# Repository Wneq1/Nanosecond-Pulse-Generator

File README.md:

# Nanosecond-Pulse-Generator
A nanosecond pulse generator is a device or electronic circuit designed to precisely generate pulses with extremely short durations, reaching the scale of single nanoseconds (1 ns = 10⁻⁹ seconds). Such a high time resolution is essential in many modern applications where extreme accuracy and fast operation are critical. In practice, nanosecond generators are used in measurement systems, telecommunications, and scientific research, enabling control and synchronization of very rapid processes. They allow for the generation of short electrical pulses with precisely defined pulse width and rise time, which form the foundation for high-performance digital and analog circuits.

An example waveform output from such a generator is illustrated in the graphic below. It exhibits a shape similar to a normal distribution with very steep rising and falling edges, and an amplitude close to the circuit’s supply voltage.

Although the datasheet of the LT1721 chip includes an example schematic of such a generator, it requires a triggering pulse from an external excitation generator. The author decided to design a circuit based on easily available and inexpensive components commonly found on the Polish market. Currently, the LT1721 chip is difficult to obtain in the country, which necessitates searching for alternative components.

The schematic of the generator is presented below:

The generator will consist of four basic blocks. The first block is a rectangular (square) wave signal generator. The next block is a delay line, followed by a block responsible for the exclusive alternative (exclusive OR). Finally, at the very end, there is a buffer that increases the current-driving capability of the generator’s output.

Rectangular Wave Generator Circuit:

The simplest rectangular wave generator circuit can be built using just three components: a resistor, a capacitor, and a NOT gate with a Schmitt trigger input. Circuits equipped with a Schmitt trigger input are characterized by hysteresis. Hysteresis is a phenomenon where the gate switches at different threshold voltage levels for the rising and falling edges of the signal. Therefore, for circuits with a Schmitt trigger input, threshold voltages for both edges and the hysteresis range are specified.

The simplest generator circuit is shown above. The operating principle of this circuit is very straightforward. Let’s assume that the switching thresholds of the Schmitt trigger gate are as follows: it switches from 1 to 0 when the input voltage exceeds 1.6 V, and from 0 to 1 when it drops to 0.8 V. At the very beginning, the capacitor is discharged, so the voltage at the input is 0 V, which is lower than the 0.8 V threshold required to switch from 0 to 1. Therefore, the output is at a high state. When the output is high, the capacitor starts charging through the resistor until the voltage exceeds 1.6 V, triggering a state change. This cycle repeats continuously.
The operating frequency is determined by the following formula, where C1 is the capacitance of the oscillating capacitor, and R1 is the resistance value in the feedback loop:

$f_0 = 1.2 / (R_1 * C_1)$

​Delay Line:

The primary purpose of the delay line is to deliver two signals to the exclusive OR (XOR) circuit with an appropriate time shift. In this project, the output from the generator is fed directly into the XOR gate, while the second connection is realized through two NOT gates. It should be noted that the signals at the input of the path have the same phase but are slightly delayed due to the use of the double NOT gates. The signal delay time depends solely on the propagation delays of the NOT gates used, which provide the necessary timing difference.

XOR Gate:

The XOR gate generates a short pulse (called a spike pulse) each time there is an edge on the output signal of the relaxation oscillator. Based on the XOR truth table, when its inputs are at different logic levels (one input is high while the other is delayed by the NOT inverters), the output goes high. This high state lasts until the delayed input also changes state, effectively turning off the generator. When both inputs are either high or low simultaneously, the output remains at 0, producing no pulse. These pulses appear in pairs, as each pulse corresponds to both the rising and falling edges of the oscillator’s output signal. The XOR gate is used here for precise detection of signal state changes, enabling the generation of very short output pulses.

Output Buffer:

Since the output of the generator is not intended to drive a heavy load, it was decided to increase the current-driving capability of the circuit by adding additional NOT gates at the output. The typical current capability of a standard logic gate ranges from about 5 to 10 mA, so it was necessary to increase this capacity to protect the circuit from accidental overload.
At the output of the XOR gate, there is a NOT gate that inverts the input signal. Following this, the actual buffer consists of three NOT gates connected in parallel. Resistors are placed at their outputs to provide impedance matching for the proper output, and a connector allows the addition of an external resistor if needed.

The complete generator schematic is shown below:

Selection of Integrated Circuits for the Generator:

When working with very fast logic circuits, it is crucial that their propagation delays are as short as possible. On the market, there are two main families of logic ICs widely used in digital electronics: HC (High-speed CMOS) and AC (Advanced CMOS). Both are based on CMOS technology but differ primarily in speed and power consumption, which determines their suitability for various applications. Understanding these differences helps in selecting the appropriate family of ICs for specific uses, especially in hobbyist and student projects.

The HC family, which includes ICs like the 74HC04, is characterized by low power consumption and higher speed compared to traditional CMOS devices. HC ICs are voltage-compatible with TTL logic, allowing them to be used in systems combining different logic technologies. They operate in a voltage range from 2 V to 6 V, making them versatile for low-voltage applications common in modern digital circuits. Due to their energy efficiency, HC gates are commonly used in projects requiring moderate speed with power savings.

The AC family, including ICs such as the 74AC86N, is an enhanced version of HC, offering significantly higher operating speeds. AC ICs have shorter propagation delays, making them ideal for applications requiring very fast switching. Although they consume slightly more power than HC devices, their high performance is essential in projects where response time is critical. They also operate within the same voltage range as HC (2 V to 6 V), maintaining versatility.

For the rectangular signal generator, the 74HCT14 gate was chosen because propagation delay is not a critical factor in this function, and it allows for a significant cost reduction. In contrast, the delay line and XOR modules use 74AC04N and 74AC86N gates. The use of AC gates results from more demanding tasks where delay time and XOR gate switching speed are crucial. The high-speed operation of these ICs enables precise signal control, which is especially important in this project. Additionally, the use of AC gates contributes to an energy-efficient design, with their low power consumption and simple power supply requirements (2 V to 6 V range) greatly simplifying the overall construction.

PCB Design:

The design will be carried out in the KiCad environment due to several key advantages. First and foremost, KiCad offers an intuitive and user-friendly interface that allows even beginners to start working on a project quickly. This makes the design process less time-consuming and more efficient.
Another important advantage of KiCad is the ability to visualize the project at every stage of work. This makes it easy to control the placement of components and routing of tracks, significantly minimizing the risk of errors and allowing for quick corrections. The software also provides extensive libraries of electronic components, which are regularly updated, greatly facilitating the selection and placement of the right parts. Additionally, KiCad allows easy generation of various production files such as Gerber files, drill files, and technical documentation, streamlining the process of ordering PCBs from manufacturers. It is also worth emphasizing that KiCad offers circuit simulation functionality, enabling preliminary testing of the circuit operation before creating a physical board. All these features together make using KiCad not only convenient but also economical and efficient.

The schematic is shown above, with component values indicated as well as a goldpin connector used to adjust the output resistance for proper impedance matching with the tested cable.
Below is the view of the PCB after the design phase:

Visualization of the PCB Layout:

View of the Assembled and Soldered PCB:

Demonstration of the Circuit Operation:

As shown in the image above, the generator is connected directly to the oscilloscope through a T-connector, with one output terminated using a 50-ohm resistor to ensure proper impedance matching with the tested cable. When testing a coaxial cable, the terminator is replaced with the cable under test, and the resulting waveforms are observed on the oscilloscope.

The oscilloscope waveform shown above indicates a peak amplitude of approximately 4.58 V, which is close to the supply voltage. The rise and fall times are around 1.9 ns, and the total pulse width is approximately 3.6 ns. These are satisfactory results given the components used in the circuit.

Finally, let us take a look at an example measurement that this device enables — cable length testing. In the context of such measurements, the key parameter is the propagation velocity factor, which for most cables is approximately 0.7. This value is especially important when calculating the actual length of the tested cable, as it directly affects measurement accuracy. For this test, a 1-meter coaxial cable is used.

The formula needed to calculate the cable length is:

$l = (c × v_p × t_m) / 2$

Where:
l – cable length

c – speed of light in vacuum (≈ 3×10⁸ m/s)

v_p – velocity factor (propagation speed in the medium)

t_m – time between the initial and reflected pulse

The propagation speed in coaxial cables is reduced to approximately 70% of the speed of light due to the dielectric material and the construction of the cable itself.

With all necessary data available, we can proceed with the basic calculation:

$l = (c × v_p × t_m) / 2=(3∙10^8  [m/s]∙0,7∙10,2∙10^(-9)  [s])/2=2,142 [m]/2=1,071 [m]$

Therefore, the calculated length of the cable using the time-domain reflectometry (TDR) method is 1.071 meters, which corresponds closely to the actual physical length of 1 meter, with only 0.71 centimeters of deviation — well within acceptable accuracy.

The aim of the project was to design and build a simple nanosecond pulse generator intended for studying signal propagation phenomena in long transmission lines, such as coaxial cables. The project is based on widely available and inexpensive components, making it accessible for students and hobbyists. Key parameters of the circuit, such as the pulse rise/fall time in the range of 1.7–1.9 ns and an amplitude close to the supply voltage (approx. 4.58 V), confirm its high effectiveness at a low production cost.
During the implementation, the author drew inspiration from the concept presented in the article "5ns pulse generator" from [polprog.net](https://polprog.net/blog/5nanos/5nanos.html), adapting the design to components readily available on the Polish market.
As part of the project, a custom PCB was designed, suitable logic ICs (from the HCT and AC families) were selected, necessary calculations were performed, and measurements confirmed the functionality of the circuit. In the future, the generator may be expanded with improved impedance matching, more powerful output buffers, or a microcontroller for automated cable length measurement.

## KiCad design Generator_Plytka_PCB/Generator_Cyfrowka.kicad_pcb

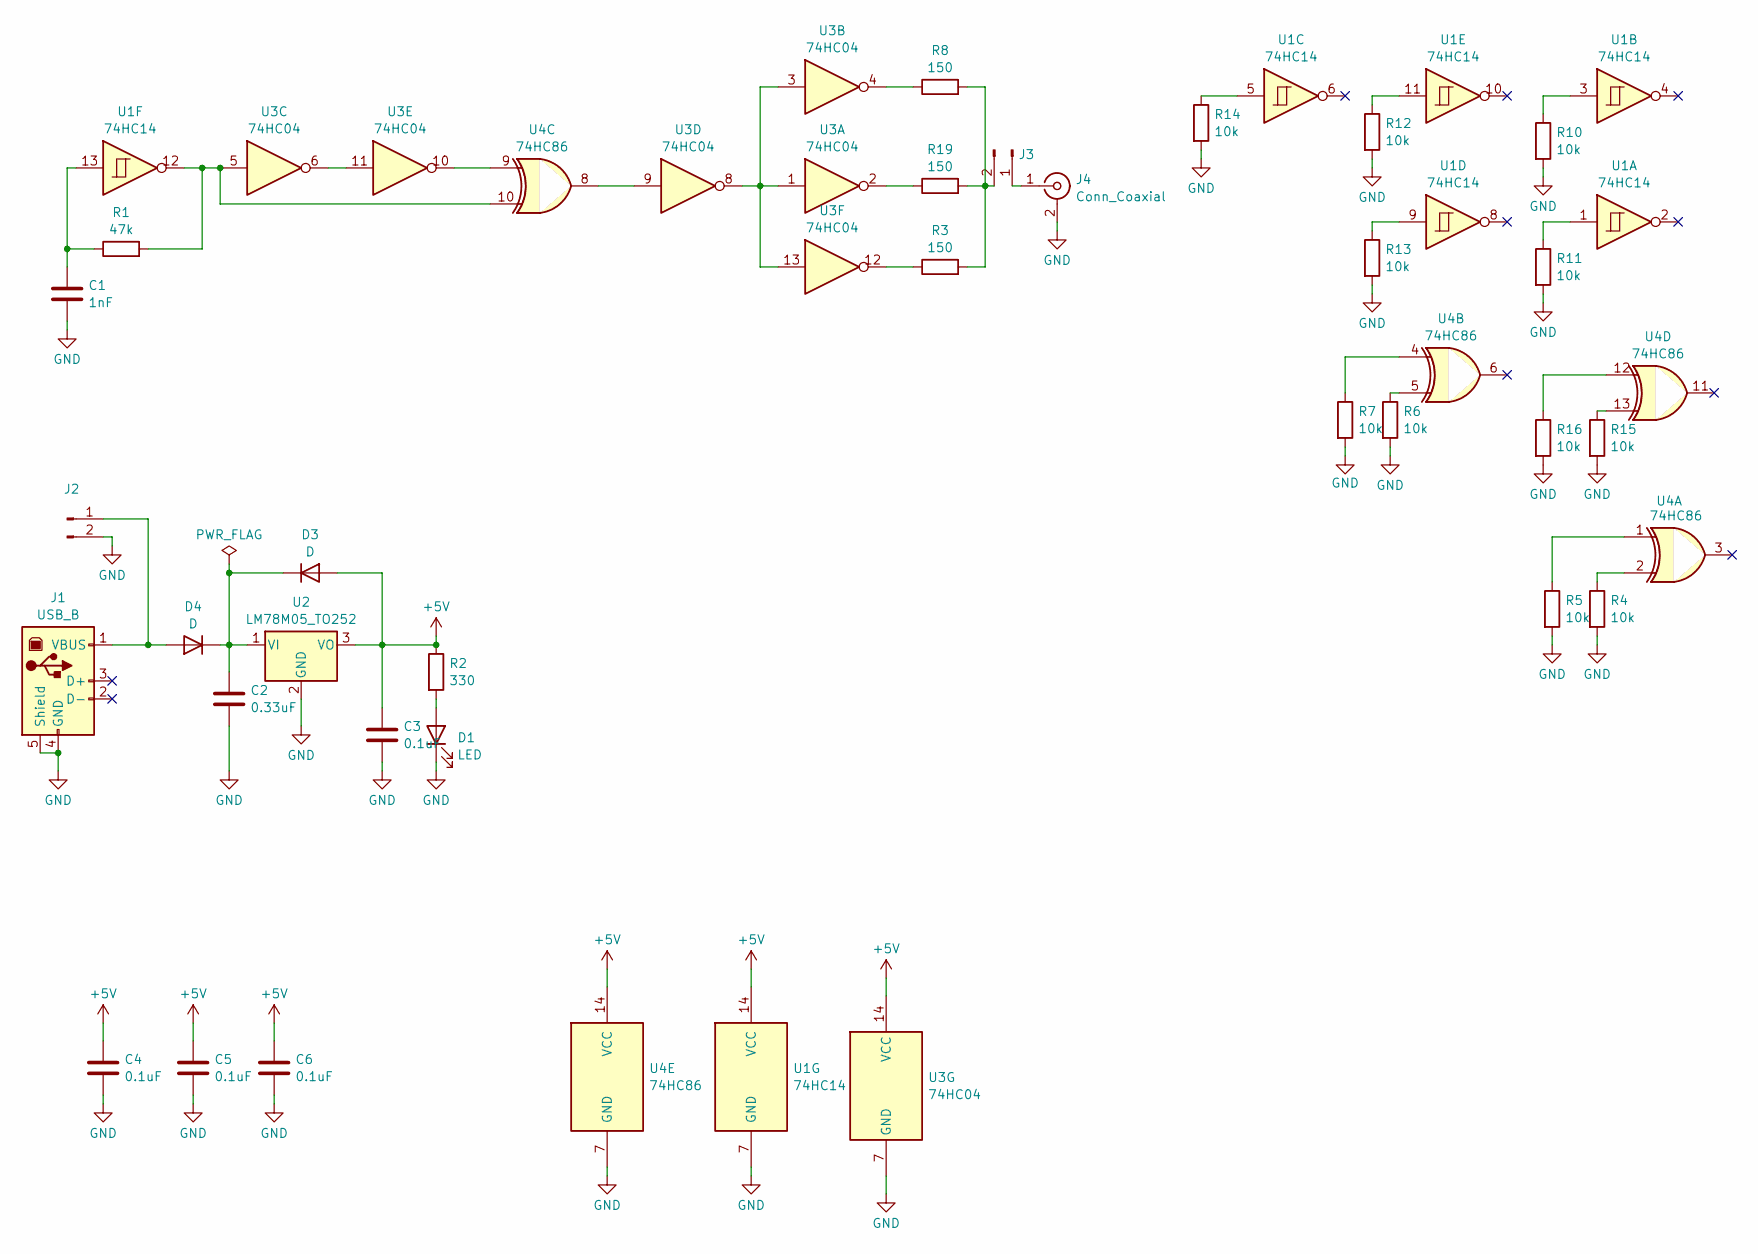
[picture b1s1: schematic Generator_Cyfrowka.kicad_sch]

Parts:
C1: 1nF; C_1206_3216Metric
C2: 0.33uF; C_1206_3216Metric
C3, C4, C5, C6: 0.1uF; C_1206_3216Metric
D1: LED; LED_1206_3216Metric
D3, D4: D; D_1206_3216Metric
J1: USB_B; USB_B_Lumberg_2411_02_Horizontal
J2, J3: Conn_01x02_Pin; PinHeader_1x02_P2.54mm_Vertical
J4: Conn_Coaxial; BNC_Amphenol_B6252HB-NPP3G-50_Horizontal
R1: 47k; R_1206_3216Metric
R2: 330; R_1206_3216Metric
R3, R8, R19: 150; R_1206_3216Metric
R4, R5, R6, R7, R10, R11, R12, R13, R14, R15, R16: 10k; R_1206_3216Metric
U1: 74HC14; DIP-14_W7.62mm
U2: LM78M05_TO252; TO-252-2
U3: 74HC04; DIP-14_W7.62mm
U4: 74HC86; DIP-14_W7.62mm

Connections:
+5V: C3.1, C4.1, C5.1, C6.1, D3.2 (A), R2.1, U1.14 (VCC), U2.3 (VO), U3.14 (VCC), U4.14 (VCC); also elsewhere on the board
GND: C1.2, C2.2, C3.2, C4.2, C5.2, C6.2, D1.1 (K), J1.4 (GND), J1.5 (Shield), J2.2, J4.2 (Ext), R4.2, R5.2, R6.2, R7.2, R10.2, R11.2, R12.2, R13.2, R14.2, R15.2, R16.2, U1.7 (GND), U2.2 (GND), U3.7 (GND), U4.7 (GND); also elsewhere on the board
unnamed: C1.1, R1.1, U1.13
unnamed: D1.2 (A), R2.2
unnamed: C2.1, D3.1 (K), D4.1 (K), U2.1 (VI)
unnamed: D4.2 (A), J1.1 (VBUS), J2.1
unnamed: J3.1, J4.1 (In)
unnamed: J3.2, R3.2, R8.2, R19.2
unnamed: R1.2, U1.12, U3.5, U4.10
unnamed: R3.1, U3.12
unnamed: R4.1, U4.2
unnamed: R5.1, U4.1
unnamed: R6.1, U4.5
unnamed: R7.1, U4.4
unnamed: R8.1, U3.4
unnamed: R10.1, U1.3
unnamed: R11.1, U1.1
unnamed: R12.1, U1.11
unnamed: R13.1, U1.9
unnamed: R14.1, U1.5
unnamed: R15.1, U4.13
unnamed: R16.1, U4.12
unnamed: R19.1, U3.2
unnamed: U3.1, U3.3, U3.8, U3.13
unnamed: U3.9, U4.8
unnamed: U3.10, U4.9
unnamed: U3.6, U3.11

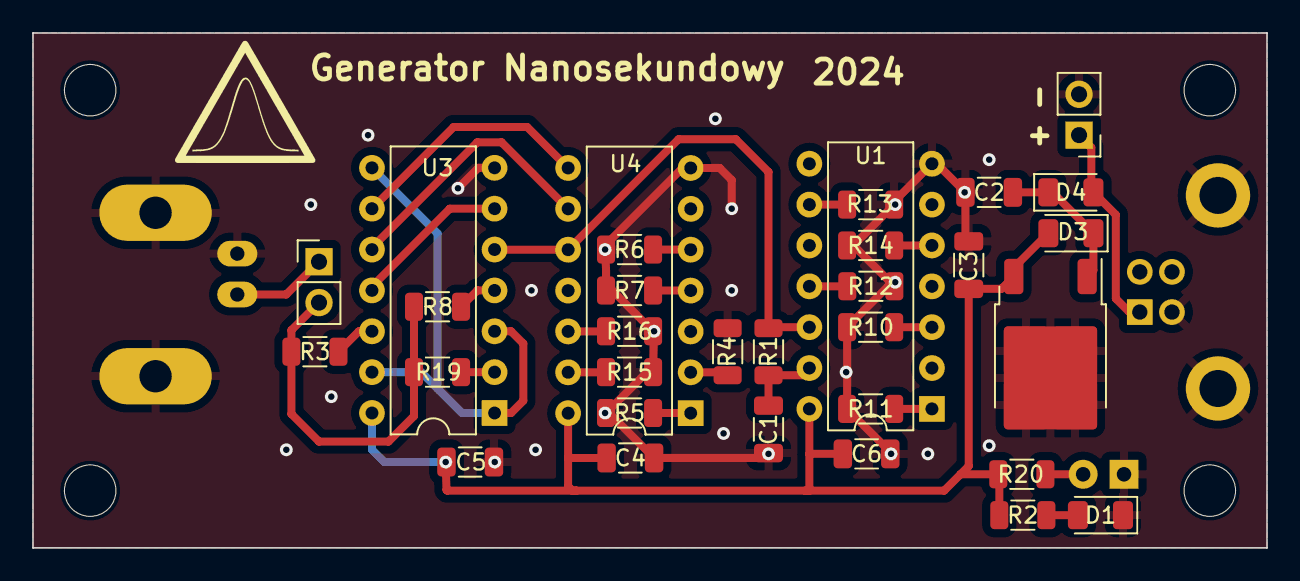
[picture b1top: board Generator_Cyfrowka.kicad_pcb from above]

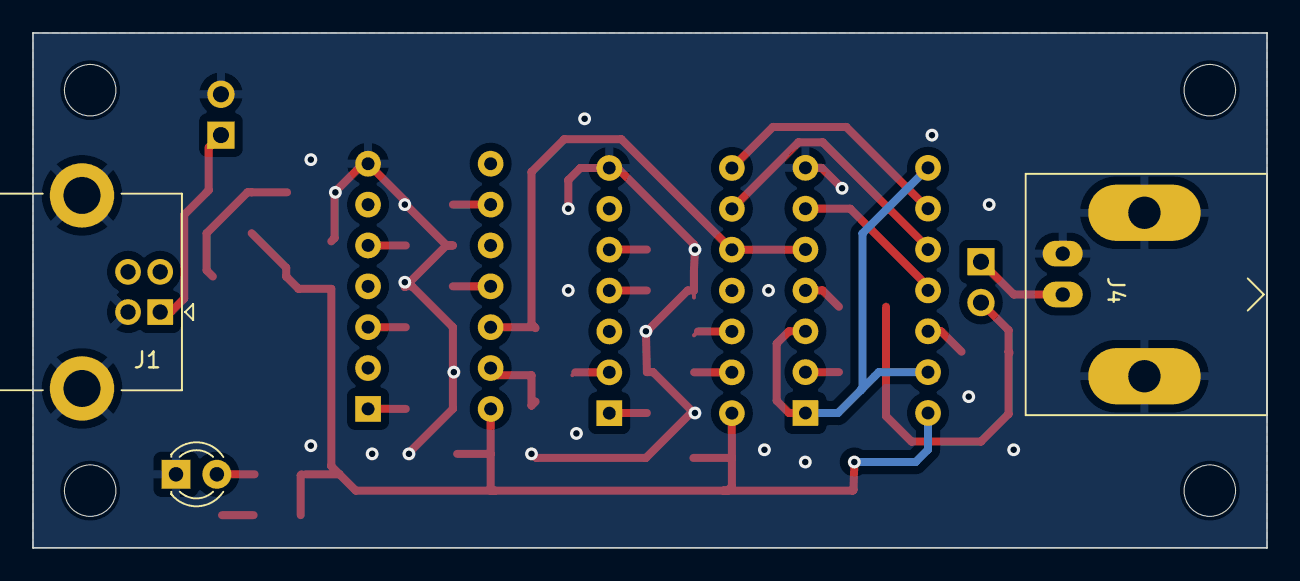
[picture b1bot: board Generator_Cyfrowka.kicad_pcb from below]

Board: 2 copper layers, 76.7 x 32.0 mm, 35 parts (3 on the bottom side), 28 nets.

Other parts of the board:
D2: LED; LED_D3.0mm_IRBlack
R20: 330; R_1206_3216Metric

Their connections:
+5V: R20.1; also elsewhere on the board
GND: D2.1 (K); also elsewhere on the board
unnamed: D2.2 (A), R20.2
